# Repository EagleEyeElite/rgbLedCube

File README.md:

# 3x3x3 RGB LED Cube

## video
 \
click image to open video

## board git conf:
[git setup](https://jnavila.github.io/plotkicadsch/) \
[example](https://github.com/John-Nagle/ttyloopdriver)

## programmer examples
```
Arduino: get terminal: avrdude -c stk500v1 -b 19200 -P /dev/ttyACM0 -p atmega1284p -t
Programmer: avrdude -c stk500 -b 115200 -P /dev/ttyACM0 -p atmega1284p -t
get all available ports: ls -l /dev/ttyACM*
```

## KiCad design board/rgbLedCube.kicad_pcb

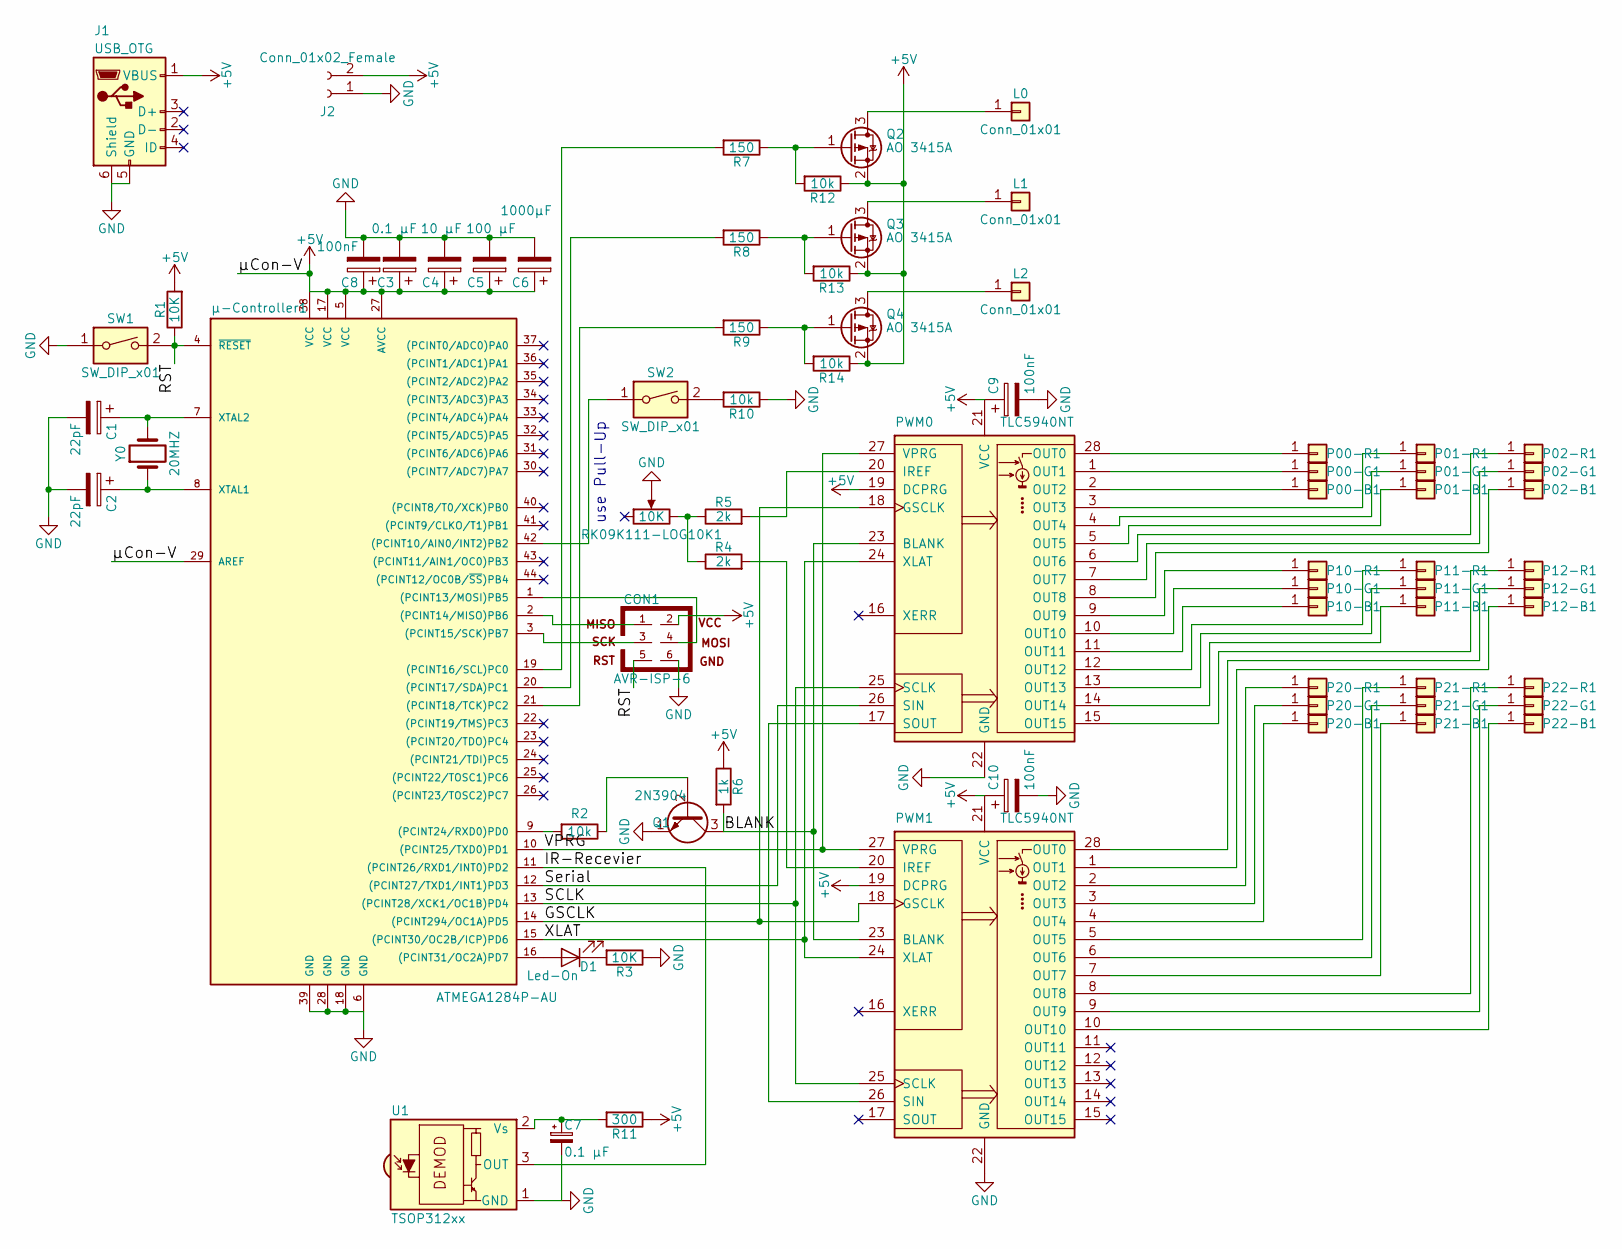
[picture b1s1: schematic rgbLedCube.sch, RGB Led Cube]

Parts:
C1, C2: 22pF; C_0603_HandSoldering
C3, C7: 0.1 µF; C_0603_HandSoldering
C4: 10 µF; CP_Elec_5x5.3
C5: 100 µF; CP_Elec_5x5.8
C6: 1000µF; CP_Elec_10x10.5
C8, C9, C10: 100nF; C_0603_HandSoldering
CON1: AVR-ISP-6; Pin_Header_Angled_2x03_Pitch2.54mm
D1: Led-On; LED_0603_HandSoldering
J1: USB_OTG; USB_Micro_Conn_Reichelt_Version_2
J2: Conn_01x02_Female; Pin_Header_Angled_1x02_Pitch2.54mm
L0, L1, L2: Conn_01x01; Pin_Header_Straight_1x01_Pitch2.54mm
P00-B1, P00-G1, P00-R1, P01-B1, P01-G1, P01-R1, P02-B1, P02-G1, P02-R1, P10-B1, P10-G1, P10-R1, P11-B1, P11-G1, P11-R1, P12-B1, P12-G1, P12-R1, P20-B1, P20-G1, P20-R1, P21-B1, P21-G1, P21-R1, P22-B1, P22-G1, P22-R1: Conn_01x01; Pin_Header_Straight_1x01_Pitch2.54mm
PWM0, PWM1: TLC5940NT; DIP-28_W7.62mm
Q1: 2N3904; TO-92_Molded_Narrow
Q2, Q3, Q4: AO 3415A; SOT-23
R1, R3: 10K; R_0805_HandSoldering
R2, R10, R12, R13, R14: 10k; R_0805_HandSoldering
R4, R5: 2k; R_0805_HandSoldering
R6: 1k; R_0805_HandSoldering
R7, R8, R9: 150; R_0805_HandSoldering
R11: 300; R_0805_HandSoldering
RK09K111-LOG10K1: 10K; Potentiometer-Alps
SW1, SW2: SW_DIP_x01; SW_Tactile_SPST_Angled_PTS645Vx83-2LFS
U1: TSOP312xx; IRReceiver_Vishay_CAST-3pin
Y0: 20MHZ; Crystal_SMD_HC49-SD
µ-Controller1: ATMEGA1284P-AU; TQFP-44_10x10mm_Pitch0.8mm

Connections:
+5V: C3.1, C4.1, C5.1, C6.1, C8.1, C9.1, C10.1, CON1.2, J1.1 (VBUS), J2.2, PWM0.19 (DCPRG), PWM0.21 (VCC), PWM1.19 (DCPRG), PWM1.21 (VCC), Q2.2 (S), Q3.2 (S), Q4.2 (S), R1.2, R6.1, R11.1, R12.1, R13.1, R14.1, µ-Controller1.5 (VCC), µ-Controller1.17 (VCC), µ-Controller1.27 (AVCC), µ-Controller1.29 (AREF), µ-Controller1.38 (VCC)
/BLANK: PWM0.23 (BLANK), PWM1.23 (BLANK), Q1.3 (C), R6.2
/GSCLK: PWM0.18 (GSCLK), PWM1.18 (GSCLK), µ-Controller1.14 ((PCINT294/OC1A)PD5)
/IR-Recevier: U1.3 (OUT), µ-Controller1.11 ((PCINT26/RXD1/INT0)PD2)
/RST: CON1.5, R1.1, SW1.2, µ-Controller1.4 (~RESET)
/SCLK: PWM0.25 (SCLK), PWM1.25 (SCLK), µ-Controller1.13 ((PCINT28/XCK1/OC1B)PD4)
/Serial: PWM0.26 (SIN), µ-Controller1.12 ((PCINT27/TXD1/INT1)PD3)
/VPRG: PWM0.27 (VPRG), PWM1.27 (VPRG), µ-Controller1.10 ((PCINT25/TXD0)PD1)
/XLAT: PWM0.24 (XLAT), PWM1.24 (XLAT), µ-Controller1.15 ((PCINT30/OC2B/ICP)PD6)
GND: C1.2, C2.2, C3.2, C4.2, C5.2, C6.2, C7.2, C8.2, C9.2, C10.2, CON1.6, J1.5 (GND), J1.6 (Shield), J2.1, PWM0.22 (GND), PWM1.22 (GND), Q1.1 (E), R3.1, R10.1, RK09K111-LOG10K1.2, SW1.1, U1.1 (GND), µ-Controller1.6 (GND), µ-Controller1.18 (GND), µ-Controller1.28 (GND), µ-Controller1.39 (GND)
unnamed: C1.1, Y0.2, µ-Controller1.7 (XTAL2)
unnamed: C2.1, Y0.1, µ-Controller1.8 (XTAL1)
unnamed: C7.1, R11.2, U1.2 (Vs)
unnamed: CON1.1, µ-Controller1.2 ((PCINT14/MISO)PB6)
unnamed: CON1.3, µ-Controller1.3 ((PCINT15/SCK)PB7)
unnamed: CON1.4, µ-Controller1.1 ((PCINT13/MOSI)PB5)
unnamed: D1.1 (K), R3.2
unnamed: D1.2 (A), µ-Controller1.16 ((PCINT31/OC2A)PD7)
unnamed: L0.1, Q2.3 (D)
unnamed: L1.1, Q3.3 (D)
unnamed: L2.1, Q4.3 (D)
unnamed: P00-B1.1, PWM0.2 (OUT2)
unnamed: P00-G1.1, PWM0.1 (OUT1)
unnamed: P00-R1.1, PWM0.28 (OUT0)
unnamed: P01-B1.1, PWM0.5 (OUT5)
unnamed: P01-G1.1, PWM0.4 (OUT4)
unnamed: P01-R1.1, PWM0.3 (OUT3)
unnamed: P02-B1.1, PWM0.8 (OUT8)
unnamed: P02-G1.1, PWM0.7 (OUT7)
unnamed: P02-R1.1, PWM0.6 (OUT6)
unnamed: P10-B1.1, PWM0.11 (OUT11)
unnamed: P10-G1.1, PWM0.10 (OUT10)
unnamed: P10-R1.1, PWM0.9 (OUT9)
unnamed: P11-B1.1, PWM0.14 (OUT14)
unnamed: P11-G1.1, PWM0.13 (OUT13)
unnamed: P11-R1.1, PWM0.12 (OUT12)
unnamed: P12-B1.1, PWM1.1 (OUT1)
unnamed: P12-G1.1, PWM1.28 (OUT0)
unnamed: P12-R1.1, PWM0.15 (OUT15)
unnamed: P20-B1.1, PWM1.4 (OUT4)
unnamed: P20-G1.1, PWM1.3 (OUT3)
unnamed: P20-R1.1, PWM1.2 (OUT2)
unnamed: P21-B1.1, PWM1.7 (OUT7)
unnamed: P21-G1.1, PWM1.6 (OUT6)
unnamed: P21-R1.1, PWM1.5 (OUT5)
unnamed: P22-B1.1, PWM1.10 (OUT10)
unnamed: P22-G1.1, PWM1.9 (OUT9)
unnamed: P22-R1.1, PWM1.8 (OUT8)
unnamed: PWM0.17 (SOUT), PWM1.26 (SIN)
unnamed: PWM0.20 (IREF), R5.2
unnamed: PWM1.20 (IREF), R4.2
unnamed: Q1.2 (B), R2.1
unnamed: Q2.1 (G), R7.1, R12.2
unnamed: Q3.1 (G), R8.1, R13.2
unnamed: Q4.1 (G), R9.1, R14.2
unnamed: R2.2, µ-Controller1.9 ((PCINT24/RXD0)PD0)
unnamed: R4.1, R5.1, RK09K111-LOG10K1.3
unnamed: R7.2, µ-Controller1.19 ((PCINT16/SCL)PC0)
unnamed: R8.2, µ-Controller1.20 ((PCINT17/SDA)PC1)
unnamed: R9.2, µ-Controller1.21 ((PCINT18/TCK)PC2)
unnamed: R10.2, SW2.2
unnamed: SW2.1, µ-Controller1.42 ((PCINT10/AIN0/INT2)PB2)

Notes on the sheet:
use Pull-Up

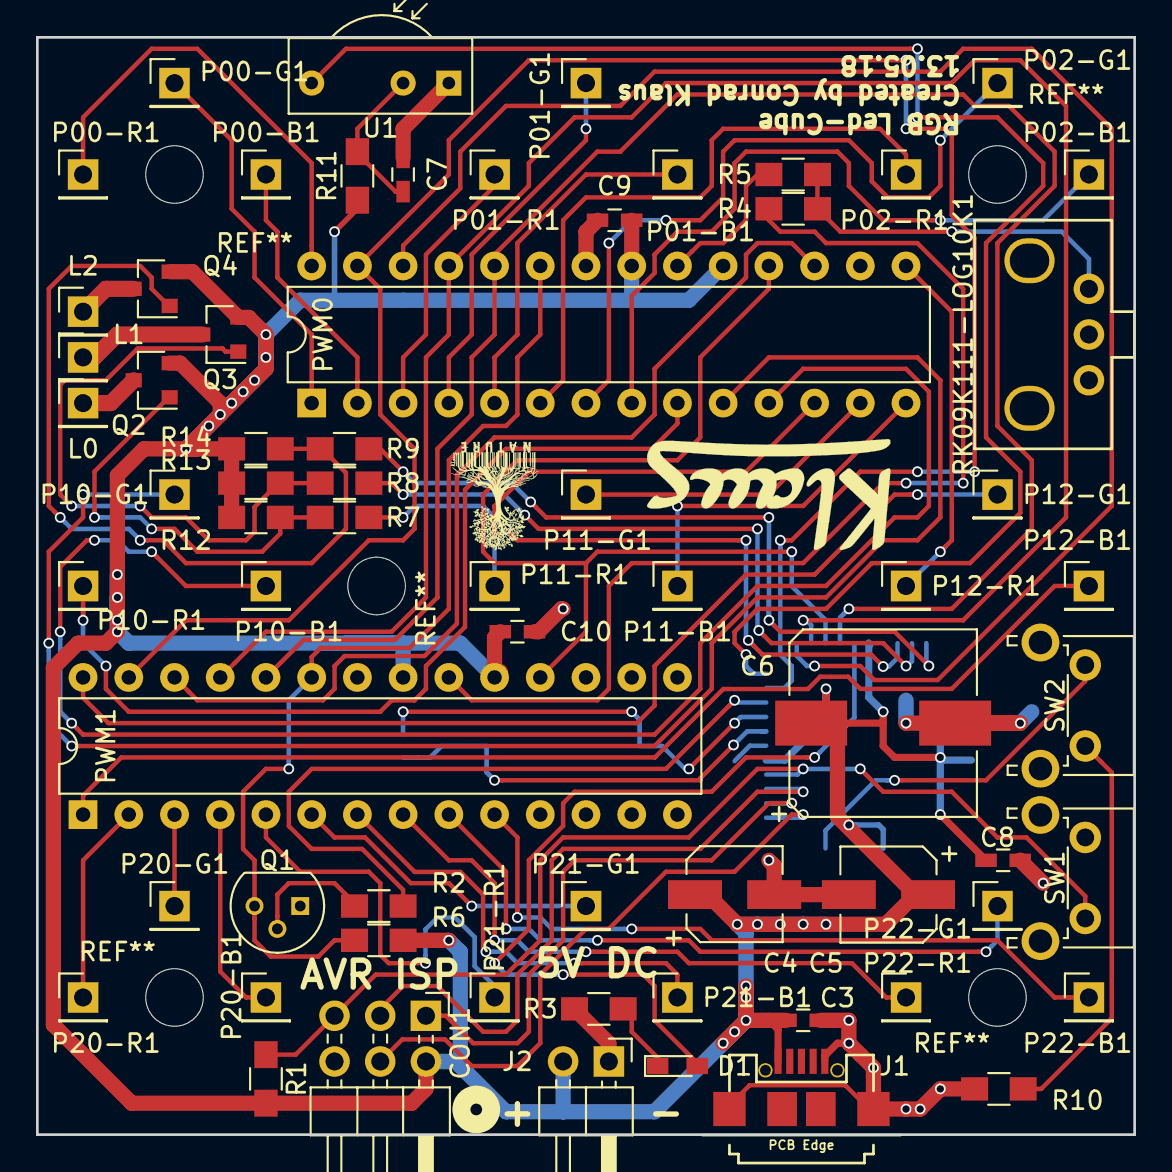
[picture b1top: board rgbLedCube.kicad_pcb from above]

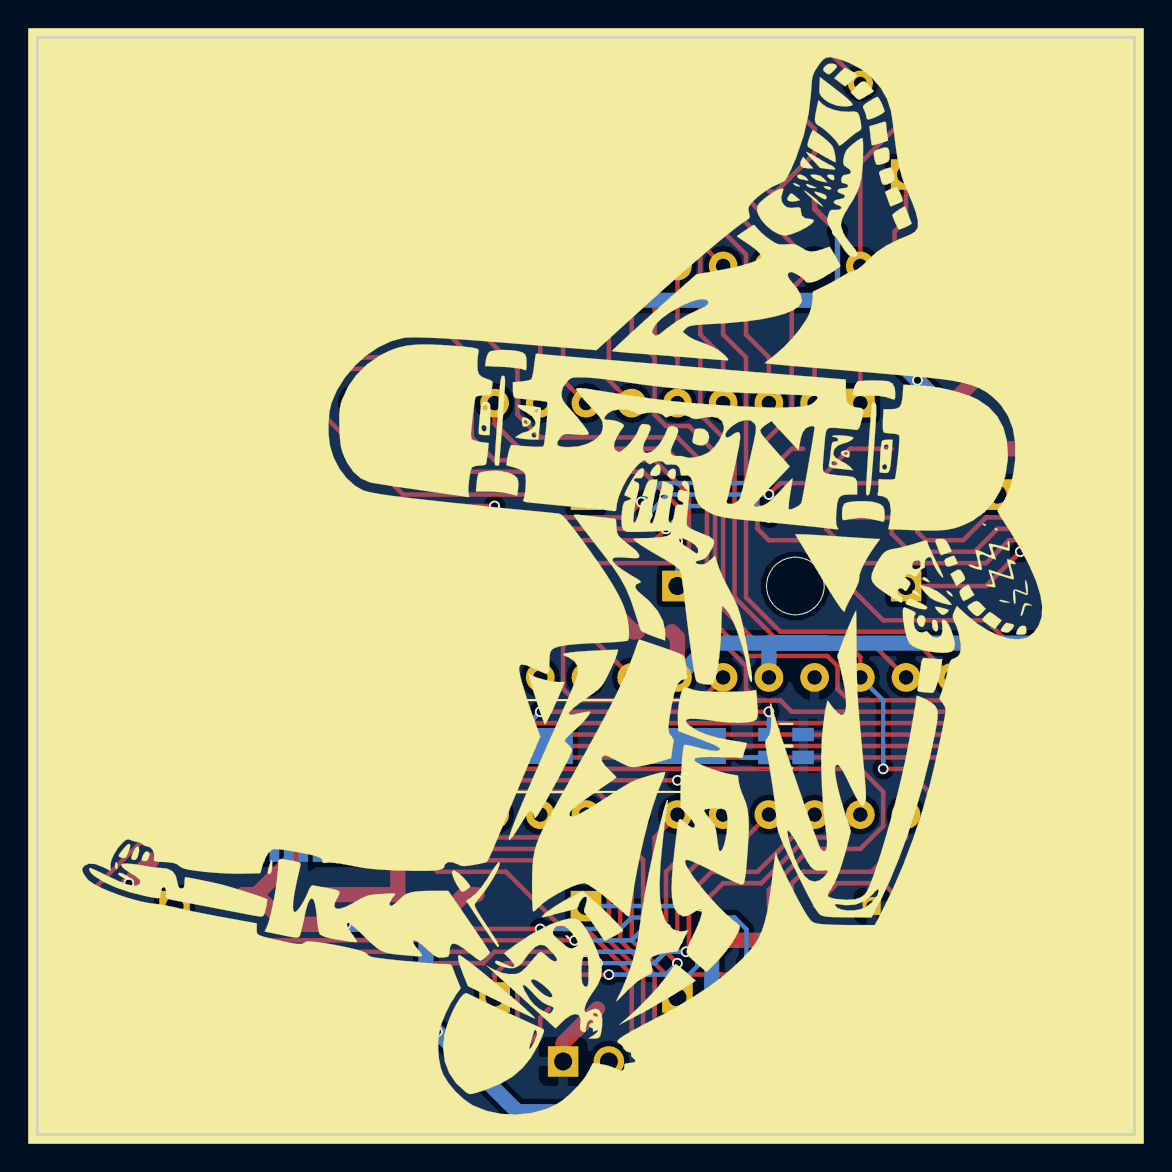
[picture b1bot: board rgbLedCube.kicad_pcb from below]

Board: 2 copper layers, 61.0 x 61.0 mm, 70 parts (4 on the bottom side), 62 nets.

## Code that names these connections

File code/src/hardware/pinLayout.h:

//
// Created by Conrad Klaus on 06.06.22.
//

#pragma once

#define SW 2    // PB2 - switch

#define Layer0 0    // PC0 - mosfet for led layer
#define Layer1 1    // PC1
#define Layer2 2    // PC2

#define BLANK 0 // PD0 - when low, it's high on the pcb and disables the tlc output
#define VPRG 1  // PD1 - sets grayscale / dot correction (dc) mode
#define IR_Rec 2    // PD2
#define SIN 3   // PD3 - serial in
#define SCLK 4  // PD4 - serial clock
#define GSCLK 5 // PD5	//OC1A - grayscale clock
#define XLAT 6  // PD6 - latches serial data into registers
#define LED 7   // PD7

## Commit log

2020-04-01 add files
2020-04-01 add demo Video
2020-04-01 add result pic
2020-04-06 add a mistake
2020-04-07 add used Colour
2020-04-17 add 2nd programmer info
2020-04-18 add Led Fix
2020-07-17 add LED Tester
2020-07-17 add DC Control for LED check
2021-06-03 include demo video in led cube
2022-03-16 add color support for plain transitions + refactoring
2022-03-17 add on/off support with IR
2022-03-17 del unused files & refactor
2022-04-06 fix: return to sleep after interrupt
2022-06-04 add asm support
2022-06-04 add software reset and fix USART interrupt
2022-06-04 add reset persistent state
2022-06-06 minimize eeprom writes
    - writes only occur after hardware resets
    - add config to disable eeprom writes
    - refactor, split led driver code into sub files
2022-06-10 simplify headers
2022-06-10 fix: blue flashing LED in display
    - remove shared state
    - functional uart transmission
    - cleanup
2022-06-10 improve button reliability
2022-06-11 wip: rotating wave with color fade
2022-06-30 Fix spelling error sin->sine
2023-02-23 wip: lots of wild changes
